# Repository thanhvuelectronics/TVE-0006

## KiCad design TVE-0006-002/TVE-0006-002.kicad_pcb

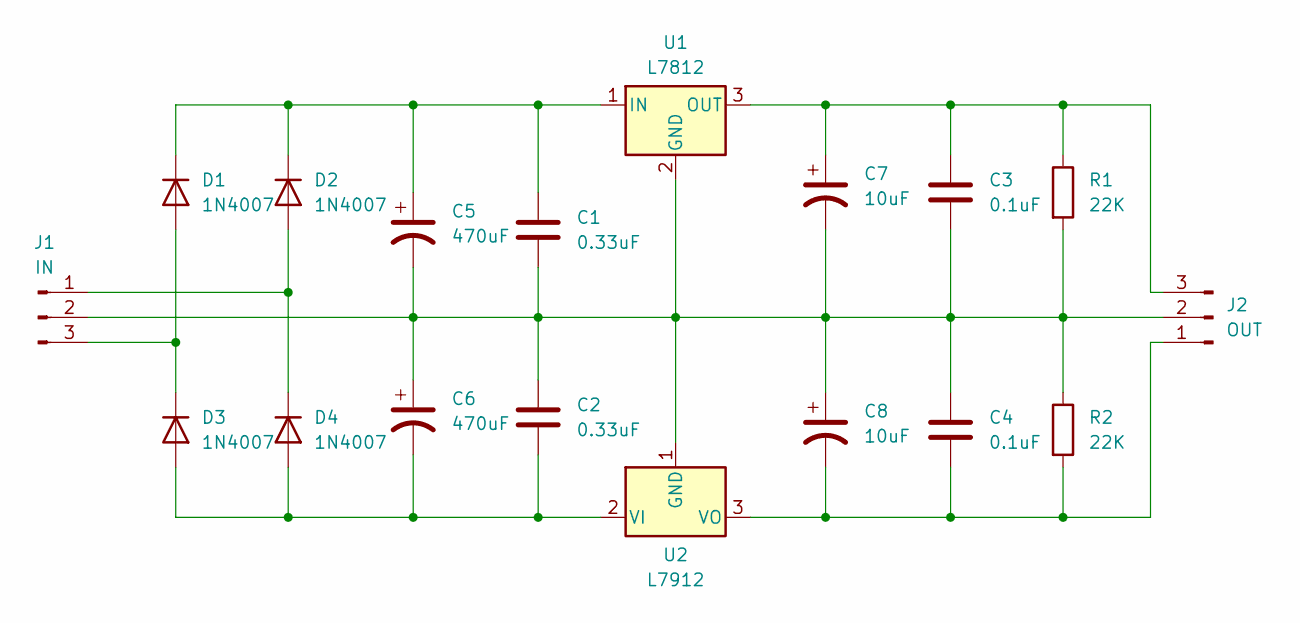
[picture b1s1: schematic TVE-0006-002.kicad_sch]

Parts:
C1, C2: 0.33uF; C_Disc_D5.0mm_W2.5mm_P5.00mm
C3, C4: 0.1uF; C_Disc_D5.0mm_W2.5mm_P5.00mm
C5, C6: 470uF; CP_Radial_D10.0mm_P5.00mm
C7, C8: 10uF; CP_Radial_D5.0mm_P2.00mm
D1, D2, D3, D4: 1N4007; D_DO-41_SOD81_P10.16mm_Horizontal
J1: IN; PinHeader_1x03_P2.54mm_Vertical
J2: OUT; PinHeader_1x03_P2.54mm_Vertical
R1, R2: 22K; R_Axial_DIN0207_L6.3mm_D2.5mm_P7.62mm_Horizontal
U1: L7812; TO-220-3_Vertical
U2: L7912; TO-220-3_Vertical

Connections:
unnamed: D1.2 (A), D3.1 (K), J1.3
unnamed: C1.1, C5.1, D1.1 (K), D2.1 (K), U1.1 (IN)
unnamed: D2.2 (A), D4.1 (K), J1.1
unnamed: C2.2, C6.2, D3.2 (A), D4.2 (A), U2.2 (VI)
unnamed: C1.2, C2.1, C3.2, C4.1, C5.2, C6.1, C7.2, C8.1, J1.2, J2.2, R1.2, R2.1, U1.2 (GND), U2.1 (GND)
unnamed: C4.2, C8.2, J2.1, R2.2, U2.3 (VO)
unnamed: C3.1, C7.1, J2.3, R1.1, U1.3 (OUT)

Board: 2 copper layers, 18 parts (0 on the bottom side), 7 nets, no tracks yet.

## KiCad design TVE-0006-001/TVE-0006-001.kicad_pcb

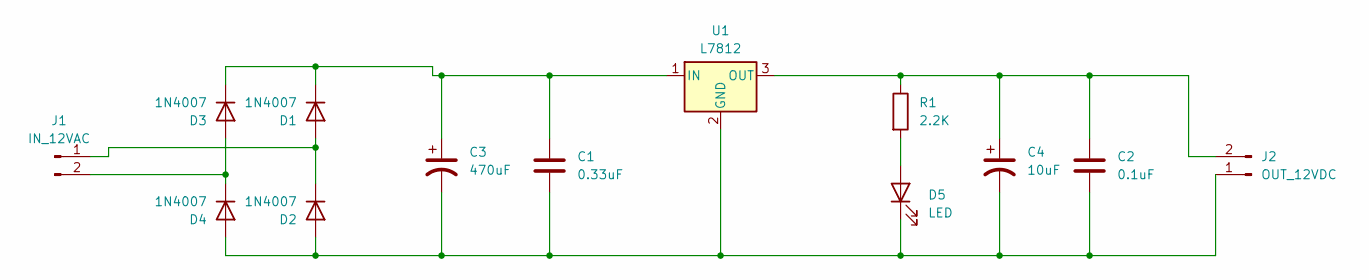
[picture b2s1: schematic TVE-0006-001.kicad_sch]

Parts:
C1: 0.33uF; C_Disc_D5.0mm_W2.5mm_P5.00mm
C2: 0.1uF; C_Disc_D5.0mm_W2.5mm_P5.00mm
C3: 470uF; CP_Radial_D10.0mm_P5.00mm
C4: 10uF; CP_Radial_D5.0mm_P2.00mm
D1, D2, D3, D4: 1N4007; D_DO-41_SOD81_P10.16mm_Horizontal
D5: LED; LED_D3.0mm
J1: IN_12VAC; PinHeader_1x02_P2.54mm_Vertical
J2: OUT_12VDC; PinHeader_1x02_P2.54mm_Vertical
R1: 2.2K; R_Axial_DIN0207_L6.3mm_D2.5mm_P7.62mm_Horizontal
U1: L7812; TO-220-3_Vertical

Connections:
unnamed: D1.2 (A), D2.1 (K), J1.1
unnamed: C1.1, C3.1, D1.1 (K), D3.1 (K), U1.1 (IN)
unnamed: C1.2, C2.2, C3.2, C4.2, D2.2 (A), D4.2 (A), D5.1 (K), J2.1, U1.2 (GND)
unnamed: D3.2 (A), D4.1 (K), J1.2
unnamed: D5.2 (A), R1.2
unnamed: C2.1, C4.1, J2.2, R1.1, U1.3 (OUT)

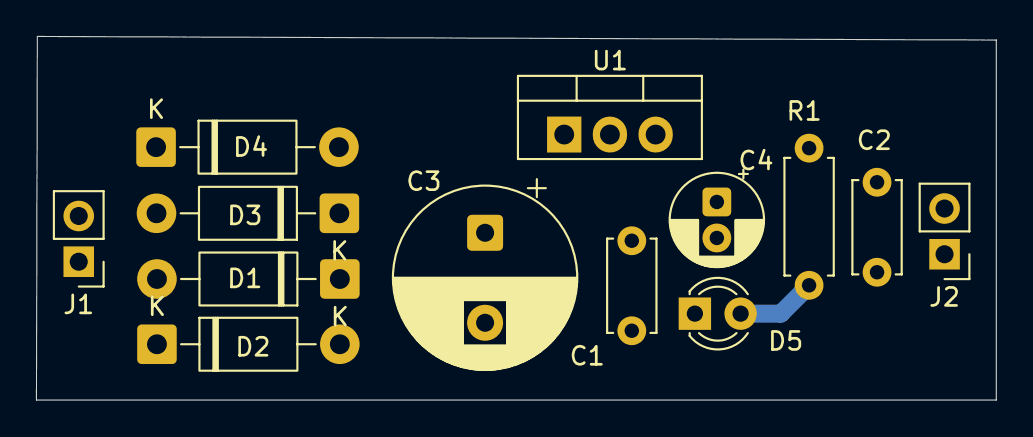
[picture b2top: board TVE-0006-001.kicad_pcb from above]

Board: 2 copper layers, 53.3 x 20.2 mm, 13 parts (0 on the bottom side), 6 nets.
